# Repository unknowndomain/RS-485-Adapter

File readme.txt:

This project is licensed under the Creative Commons License:

Attribution-ShareAlike 3.0 Unported
http://creativecommons.org/licenses/by-sa/3.0/

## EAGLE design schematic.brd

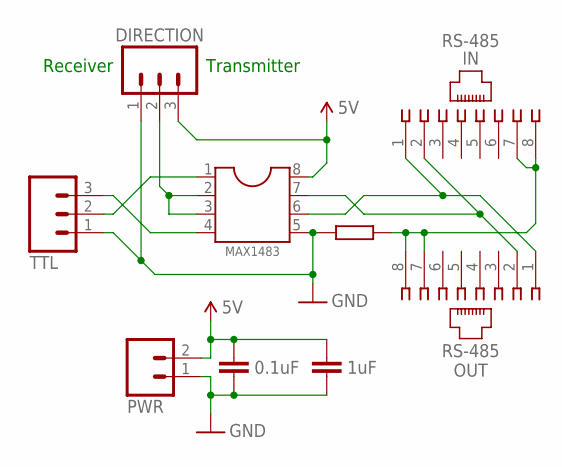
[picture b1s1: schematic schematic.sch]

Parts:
B1: 100R; 0207/10
C1: 0.1uF; C025-025X050
C2: 1uF; CAP-PTH-5MM
DIRECTION: M03LOCK; 1X03_LOCK
IN: RS-485; 215877-4
MAX1483: DIL8S; SOCKET-08
OUT: RS-485; 215877-4
PWR: M023.5MM; SCREWTERMINAL-3.5MM-2
TTL: M03SCREW; SCREWTERMINAL-3.5MM-3

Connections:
5V: C1.1, C2.2, DIRECTION.3, MAX1483.8, PWR.2
GND: B1.1, C1.2, C2.1, DIRECTION.1, MAX1483.5, PWR.1, TTL.1
unnamed: DIRECTION.2, MAX1483.2, MAX1483.3
unnamed: MAX1483.4, TTL.3
unnamed: MAX1483.1, TTL.2
unnamed: B1.2, IN.7, IN.8, OUT.7, OUT.8
unnamed: IN.1, MAX1483.6, OUT.1
unnamed: IN.2, MAX1483.7, OUT.2

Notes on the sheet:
Transmitter
Receiver

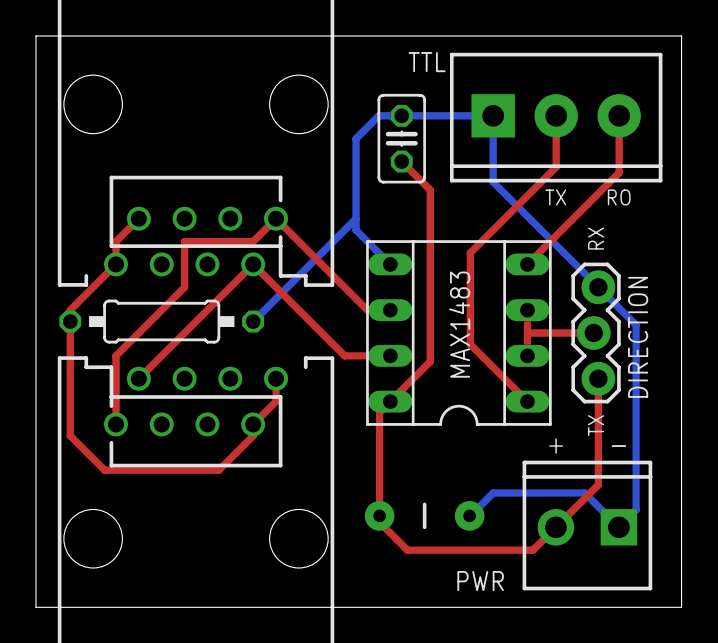
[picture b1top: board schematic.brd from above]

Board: 2 copper layers, 35.9 x 31.7 mm, 9 parts (0 on the bottom side), 8 nets.

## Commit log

2012-12-05 Added simple readme.txt

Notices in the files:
parts and their libraries:
SparkFun: Licensing: CC v3.0 Share-Alike You are welcome to use this library for commercial purposes.
